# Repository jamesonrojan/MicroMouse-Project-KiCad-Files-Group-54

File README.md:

# MicroMouse Project KiCad Files Group 54
 Contains the KiCad files for EE3088F 2025 Project PCB Files Group 54 RDJTHA001 JMSROJ001

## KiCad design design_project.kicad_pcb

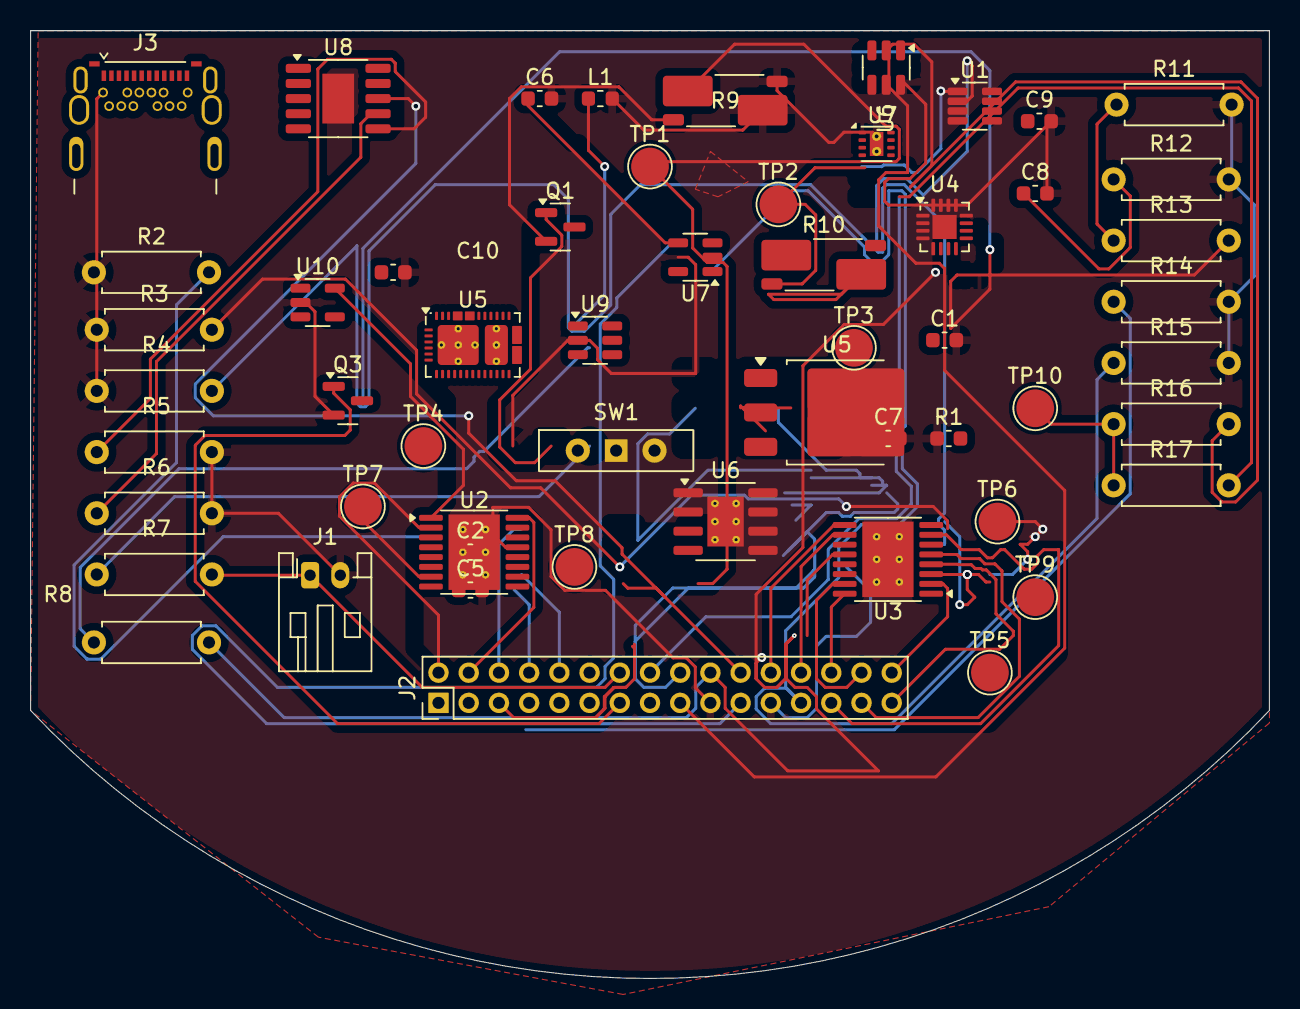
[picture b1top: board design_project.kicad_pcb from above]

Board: 2 copper layers, 82.0 x 62.7 mm, 55 parts (0 on the bottom side), 50 nets.

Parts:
C1, C2: 0.1µ; C_0603_1608Metric
C5, C6, C7, C10: 10µ; C_0603_1608Metric
C8, C9: 4.7µ; C_0603_1608Metric
J1: Conn_01x02; JST_PH_S2B-PH-K_1x02_P2.00mm_Horizontal
J2: Conn_02x16_Top_Bottom; PinHeader_2x16_P2.00mm_Vertical
J3: USB_C_Receptacle_PowerOnly_6P; USB_C_Receptacle_CNCTech_C-ARA1-AK51X
L1: 227µ; L_0603_1608Metric
Q1: AO3401CI-ES; SOT-23
Q3: 2N7002; SOT-23
R1: 0.5; C_0603_1608Metric
R2, R3, R4: 0.5; R_Axial_DIN0207_L6.3mm_D2.5mm_P7.62mm_Horizontal
R5, R6: 5.1K; R_Axial_DIN0207_L6.3mm_D2.5mm_P7.62mm_Horizontal
R7: 1M; R_Axial_DIN0207_L6.3mm_D2.5mm_P7.62mm_Horizontal
R8: 10K; R_Axial_DIN0207_L6.3mm_D2.5mm_P7.62mm_Horizontal
R9: 0.15; R_Shunt_Vishay_WSK2512_6332Metric_T2.21mm
R10: 0.5; R_Shunt_Vishay_WSK2512_6332Metric_T2.21mm
R11: 6K; R_Axial_DIN0207_L6.3mm_D2.5mm_P7.62mm_Horizontal
R12: 2K; R_Axial_DIN0207_L6.3mm_D2.5mm_P7.62mm_Horizontal
R13: 4K; R_Axial_DIN0207_L6.3mm_D2.5mm_P7.62mm_Horizontal
R14, R15: 100K; R_Axial_DIN0207_L6.3mm_D2.5mm_P7.62mm_Horizontal
R16, R17: 4.7K; R_Axial_DIN0207_L6.3mm_D2.5mm_P7.62mm_Horizontal
SW1: SW_Wuerth_450301014042; SW_Slide-03_Wuerth-WS-SLTV_10x2.5x6.4_P2.54mm
TP1, TP2, TP3, TP4, TP5, TP6, TP7, TP8, TP9, TP10: TestPoint; TestPoint_Pad_D2.5mm
U1: INA219AIDCNR; SOT-23-8
U2, U3: DRV8833PWP; HTSSOP-16-1EP_4.4x5mm_P0.65mm_EP3.4x5mm_Mask2.46x2.31mm_The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
U4: BQ24075RGTR; VQFN-16-1EP_3x3mm_P0.5mm_EP1.6x1.6mm
U5: TPS25730DREFR; Texas_REF0038A_WQFN-38-2EP_6x4mm_P0.4
U5#2: AMS1117CD-3.3; TO-252-3_TabPin2
U6: TPS22929DDBVR; SOT-23-6
U6#2: TP4056-42-ESOP8; SOIC-8-1EP_3.9x4.9mm_P1.27mm_EP2.41x3.3mm_ThermalVias
U7, U10: AP22804AW5; SOT-23-5
U7#2: TPS62160DSGR; WSON-8-1EP_2x2mm_P0.5mm_EP0.9x1.6mm_ThermalVias
U8: CH224K; SSOP-10-1EP_3.9x4.9mm_P1mm_EP2.1x3.3mm
U9: MT3608L; SOT-23-6

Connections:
3.3V: J2.18, R10.1, R16.1, R17.1, TP10.1, U1.4 (VS), U1.8 (A1), U5#2.2 (VO)
5V: C5.1, C7.1, C8.1, C9.1, J2.20, R8.2, R12.1, TP9.1, U2.1 (~SLEEP), U2.12 (VM), U3.1 (~SLEEP), U3.12 (VM), U5#2.3 (VI), U7.5 (IN), U10.5 (IN)
Battery: J1.1, J2.14, Q1.2 (S), R7.2, R9.2
CTRL_EXT_LOAD1: J2.25, R15.1, U7.4 (EN)
CTRL_EXT_LOAD2: J2.7, R14.1, U10.4 (EN)
EXT_LOAD1 _OUT: C6.1, J2.21, U7.1 (OUT)
EXT_LOAD2_OUT: C10.1, J2.11, U10.1 (OUT)
FAST_CHARGE-CTRL: J2.13, Q3.1 (G)
GND: C1.2, C2.2, C5.2, C6.2, C7.2, C8.2, C9.2, C10.2, J1.2, J2.19, J2.23, J3.A12 (GND), J3.B12 (GND), L1.2, Q3.2 (S), R1.1, R2.1, R3.1, R4.1, R5.2, R6.2, R9.3, R9.4, R11.2, R12.2, R14.2, R15.2, SW1.2 (C), U1.3 (GND), U1.7 (A0), U2.13 (GND), U2.17 (GND), U3.13 (GND), U3.17 (GND), U4.7 (~PGOOD), U4.8 (VSS), U4.14 (TMR), U4.17 (VSS), U5#2.1 (GND), U6.4 (VIN), U6#2.3 (GND), U7.2 (GND), U7#2.1 (PGND), U7#2.4 (AGND), U7#2.9 (PAD), U8.11 (GND), U9.2 (GND), U10.2 (GND)
High Voltage (9V): J2.22, U6#2.4 (V_{CC}), U8.8 (VBUS)
I2C1_SCL: J2.16, R17.2, U1.5 (SCL)
I2C1_SDA: J2.17, R16.2, U1.6 (SDA)
MOTOR1_A_OUT: J2.32, TP5.1, U3.2 (AOUT1)
MOTOR1_B_OUT: J2.31, TP6.1, U3.4 (AOUT2)
MOTOR1_CTRL1: J2.28, U3.16 (AIN1)
MOTOR1_CTRL2: J2.30, U3.15 (AIN2)
MOTOR2_A_OUT: J2.2, TP3.1, U2.2 (AOUT1)
MOTOR2_B_OUT: J2.1, TP4.1, U2.4 (AOUT2)
MOTOR2_CTRL1: J2.4, U2.16 (AIN1)
MOTOR2_CTRL2: J2.6, U2.15 (AIN2)
MOTOR3_A_OUT: J2.27, U3.7 (BOUT1)
MOTOR3_B_OUT: J2.29, U3.5 (BOUT2)
MOTOR3_CTRL1: J2.24, U3.9 (BIN1)
MOTOR3_CTRL2: J2.26, U3.10 (BIN2)
MOTOR4_A_OUT: J2.3, TP7.1, U2.7 (BOUT1)
MOTOR4_B_OUT: J2.5, TP8.1, U2.5 (BOUT2)
MOTOR4_CTRL1: J2.8, U2.9 (BIN1)
MOTOR4_CTRL2: J2.10, U2.10 (BIN2)
unnamed: U4.2 (BAT), U4.3 (BAT)
unnamed: Q1.1 (G), SW1.1 (B)
unnamed: Q3.3 (D), R13.2
unnamed: U4.10 (OUT), U4.11 (OUT)
unnamed: R7.1, SW1.3 (A)
unnamed: R10.2, TP2.1, U1.1 (IN+)
unnamed: R10.3, U1.2 (IN-)
unnamed: R2.2, U2.3 (AISEN)
unnamed: R1.2, U2.6 (BISEN)
unnamed: C1.1, U2.14 (VINT)
unnamed: R3.2, U3.3 (AISEN)
unnamed: R4.2, U3.6 (BISEN)
unnamed: C2.1, U3.14 (VINT)
unnamed: U5.11 (GND), U5.12 (GND), U5.14 (GND), U5.16 (GND), U5.17 (GND), U5.31 (GND), U5.34 (GND), U5.39 (GND)
unnamed: R9.1, TP1.1, U6#2.5 (BAT)
unnamed: R11.1, R13.1, U6#2.2 (PROG)
unnamed: R6.1, U8.7 (CC1)
unnamed: R5.1, U8.6 (CC2)
unnamed: J3.A9 (VBUS), J3.B9 (VBUS), U8.1 (VDD)
unnamed: R8.1, U9.3 (FB)
unnamed: L1.1, U9.1 (SW)
Vin: Q1.3 (D), R10.4, U4.13 (IN), U7#2.2 (VIN), U7#2.3 (EN), U9.4 (EN), U9.5 (IN)

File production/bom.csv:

Designator,Footprint,Quantity,Value,LCSC Part #
C1,0603,1,0.1µ,C1525
"C10, C6, C7",0603,3,10µ,
C2,0603,1,0.1µ,
C5,0603,1,10µ,C19702
C8,0603,1,4.7µ,C19666
C9,0603,1,4.7µ,
J1,JST_PH_S2B-PH-K_1x02_P2.00mm_Horizontal,1,Conn_01x02,
J2,PinHeader_2x16_P2.00mm_Vertical,1,Conn_02x16_Top_Bottom,C339450
J3,USB_C_Receptacle_CNCTech_C-ARA1-AK51X,1,USB_C_Receptacle_PowerOnly_6P,C393939
L1,0603,1,227µ,C10151
Q1,SOT-23,1,AO3401CI-ES,C21713833
Q3,SOT-23,1,2N7002,C8545
R1,0603,1,0.5,C459677
R10,R_Shunt_Vishay_WSK2512_6332Metric_T2.21mm,1,0.5,C459677
R11,R_Axial_DIN0207_L6.3mm_D2.5mm_P7.62mm_Horizontal,1,6K,C23189
R12,R_Axial_DIN0207_L6.3mm_D2.5mm_P7.62mm_Horizontal,1,2K,C22975
R13,R_Axial_DIN0207_L6.3mm_D2.5mm_P7.62mm_Horizontal,1,4K,C22978
"R14, R15",R_Axial_DIN0207_L6.3mm_D2.5mm_P7.62mm_Horizontal,2,100K,C25803
"R16, R17",R_Axial_DIN0207_L6.3mm_D2.5mm_P7.62mm_Horizontal,2,4.7K,C23162
R2,R_Axial_DIN0207_L6.3mm_D2.5mm_P7.62mm_Horizontal,1,0.5,C2934369
"R3, R4",R_Axial_DIN0207_L6.3mm_D2.5mm_P7.62mm_Horizontal,2,0.5,
"R5, R6",R_Axial_DIN0207_L6.3mm_D2.5mm_P7.62mm_Horizontal,2,5.1K,C23186
R7,R_Axial_DIN0207_L6.3mm_D2.5mm_P7.62mm_Horizontal,1,1M,C22935
R8,R_Axial_DIN0207_L6.3mm_D2.5mm_P7.62mm_Horizontal,1,10K,C25804
R9,R_Shunt_Vishay_WSK2512_6332Metric_T2.21mm,1,0.15,C169881
SW1,SW_Slide-03_Wuerth-WS-SLTV_10x2.5x6.4_P2.54mm,1,SW_Wuerth_450301014042,C6558197
"TP1, TP10, TP2, TP3, TP4, TP5, TP6, TP7, TP8, TP9",TestPoint_Pad_D2.5mm,10,TestPoint,
U1,SOT-23-8,1,INA219AIDCNR,C87469
U10,SOT-23-5,1,AP22804AW5,C3001659
"U2, U3",HTSSOP-16-1EP_4.4x5mm_P0.65mm_EP3.4x5mm_Mask2.46x2.31mm_ThermalVias,2,DRV8833PWP,C50506
U4,VQFN-16-1EP_3x3mm_P0.5mm_EP1.6x1.6mm,1,BQ24075RGTR,C15464
U5_2,Texas_REF0038A_WQFN-38-2EP_6x4mm_P0.4,1,TPS25730DREFR,C347249
U5,TO-252-3_TabPin2,1,AMS1117CD-3.3,
U6_2,SOT-23-6,1,TPS22929DDBVR,C16581
U6,SOIC-8-1EP_3.9x4.9mm_P1.27mm_EP2.41x3.3mm_ThermalVias,1,TP4056-42-ESOP8,
U7_2,SOT-23-5,1,AP22804AW5,C324077
U7,WSON-8-1EP_2x2mm_P0.5mm_EP0.9x1.6mm_ThermalVias,1,TPS62160DSGR,
U8,SSOP-10-1EP_3.9x4.9mm_P1mm_EP2.1x3.3mm,1,CH224K,C970725
U9,SOT-23-6,1,MT3608L,C2932326

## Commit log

2025-04-08 First submission
2025-05-04 2nd round
